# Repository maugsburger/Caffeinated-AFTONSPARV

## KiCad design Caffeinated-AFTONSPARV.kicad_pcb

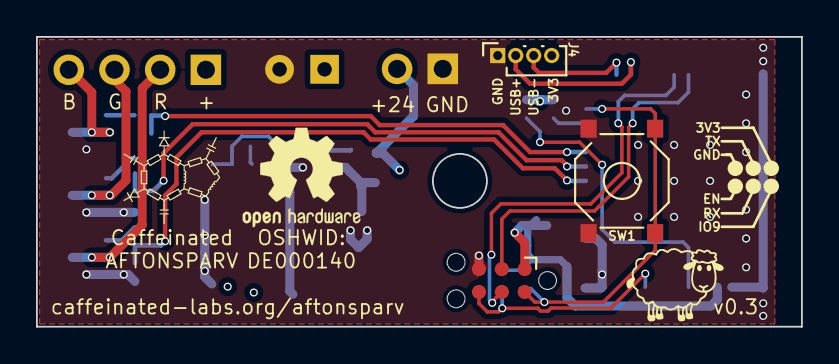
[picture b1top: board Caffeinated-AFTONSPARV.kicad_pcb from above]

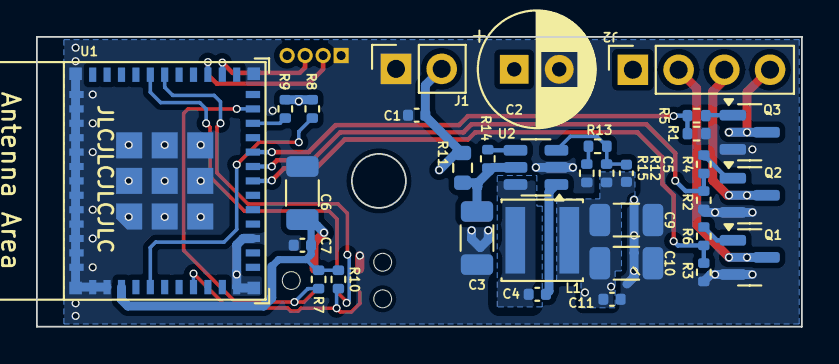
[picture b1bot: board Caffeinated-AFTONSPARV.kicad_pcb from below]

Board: 4 copper layers, 42.5 x 16.1 mm, 37 parts (33 on the bottom side), 26 nets.

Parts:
C1: 100nF 50V; C_0402_1005Metric
C2: 100µF 35V; CP_Radial_D6.3mm_P2.50mm
C3, C6, C9, C10: 4.7uF; C_1206_3216Metric
C4, C7, C11: 100nF; C_0402_1005Metric
C5: 22pF; C_0402_1005Metric
J1: PWR; PinSocket_1x02_P2.54mm_Vertical
J2: LED; PinSocket_1x04_P2.54mm_Vertical
J3: TagConnect; Tag-Connect_TC2030-IDC-NL_2x03_P1.27mm_Vertical
J4: USB; PinSocket_1x04_P1.00mm_Vertical
L1: 10uH; L_Sunlord_SWPA4030S
Q1, Q2, Q3: AO3400A; SOT-23
R1, R2, R3, R7, R8, R9, R10, R14: 10kΩ; R_0402_1005Metric
R4, R5, R6: 22Ω; R_0402_1005Metric
R11: 1Ω; R_0603_1608Metric
R12: 100kΩ; R_0402_1005Metric
R13: 22kΩ; R_0402_1005Metric
R15: 100Ω; R_0402_1005Metric
SW1: SW_Push; YTS-C005
U1: ESP32-C3-MINI-1-[H/N]4; ESP32-C3-MINI-1
U2: SY8201ABC; SOT-23-6
sheep: LOGO

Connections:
+3.3V: C5.2, C6.1, C7.1, C9.1, C10.1, C11.1, J3.1 (VCC), J4.4, L1.2, R7.1, R8.1, R9.1, R10.1, R12.1, U1.3 (3V3)
+24V: C1.1, C2.1, J1.2, J2.1, R11.1
EN: J3.6 (EN), R10.2, U1.8 (EN/CHIP_PU)
GND: C1.2, C2.2, C3.2, C6.2, C7.2, C9.2, C10.2, C11.2, J1.1, J3.5 (GND), J4.1, Q1.2 (S), Q2.2 (S), Q3.2 (S), R1.2, R2.2, R3.2, R15.2, SW1.1, U1.1 (GND), U1.2 (GND), U1.11 (GND), U1.14 (GND), U1.36 (GND), U1.37 (GND), U1.38 (GND), U1.39 (GND), U1.40 (GND), U1.41 (GND), U1.42 (GND), U1.43 (GND), U1.44 (GND), U1.45 (GND), U1.46 (GND), U1.47 (GND), U1.48 (GND), U1.49 (GND), U1.50 (GND), U1.51 (GND), U1.52 (GND), U1.53 (GND), U2.2 (GND)
IO9: J3.2 (IO0/IO9), R7.2, SW1.2, U1.23 (GPIO9)
LED-B: R1.1, R5.1, U1.20 (GPIO6)
LED-G: R2.1, R4.1, U1.19 (GPIO5/ADC2_CH0)
LED-R: R3.1, R6.1, U1.18 (GPIO4/ADC1_CH4)
unnamed: J2.2, Q1.3 (D)
unnamed: J2.3, Q2.3 (D)
unnamed: J2.4, Q3.3 (D)
unnamed: Q1.1 (G), R6.2
unnamed: Q2.1 (G), R4.2
unnamed: Q3.1 (G), R5.2
unnamed: R13.2, R15.1
unnamed: R8.2, U1.5 (GPIO2/ADC1_CH2)
unnamed: R9.2, U1.22 (GPIO8)
unnamed: C4.2, U2.1 (BS)
unnamed: R14.2, U2.4 (EN)
unnamed: C5.1, R12.2, R13.1, U2.3 (FB)
unnamed: C3.1, R11.2, R14.1, U2.5 (IN)
unnamed: C4.1, L1.1, U2.6 (LX)
RX: J3.4 (RX), U1.30 (GPIO20/U0RXD)
TX: J3.3 (TX), U1.31 (GPIO21/U0TXD)
USB-D+: J4.2, U1.27 (GPIO19/USB_D+)
USB-D-: J4.3, U1.26 (GPIO18/USB_D-)

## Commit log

2024-12-19 optimize bom for jlcpcb basic parts
2024-12-19 jlcpcb production files
